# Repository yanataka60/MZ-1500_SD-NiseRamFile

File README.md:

# MZ-1500_SD+偽RAMFILE複合ボード

しっぽいいんちょさんが作られた「偽RAMFILE for MZ-1500」とMZ-1500_SDを合体させたボードです。

MZ-1500_SD: https://github.com/yanataka60/MZ-1500_SD

偽RAMFILE for MZ-1500: https://github.com/shippoiincho/niseramfile

偽RAMFILE for MZ-1500のMZ-1R12 SRAMメモリをMZ-1500_SD起動用に使うことで一枚のボードにまとめています。

機能の詳細についてはそれぞれのウェブページを参照してください。

## 回路図
　KiCadフォルダ内のMZ-1500_SD+NRF.pdfを参照してください。

[回路図](https://github.com/yanataka60/MZ-1500_SD-NiseRamFile/blob/main/Kicad/MZ-1500_SD%2BNRF.pdf)

|番号|品名|数量|備考|
| ------------ | ------------ | ------------ | ------------ |
||J2、J3のいずれか|||
|J2|Micro_SD_Card_Kit|1|秋月電子通商 AE-microSD-LLCNV (注1)|
|J3|MicroSD Card Adapter|1|Arduino等に使われる5V電源に対応したもの(注3)|
|J4,J5|ピンソケット2x15Pin|2|RP2350Bマイコンボード用,秋月電子通商 FHU-2x42SGなど|
|J6|VGA用基板ソケット 3列15ピン|1|マルツ DJ-VGA14.5など(注4)|
|U1|74LS04|1||
|U2|74LS30|1||
|U3|8255|1||
|U4|Arduino_Pro_Mini_5V|1|Atmega328版を使用 168版は不可。(注2)|
||RP2350Bボード(Raspberry Pi Pico 2)|1|Amazon WA00021 RP2350Bマイコンボードなど|
|C1-C3|積層セラミックコンデンサ 0.1uF|3||
|C4|電解コンデンサ 16v100uF|1||
|D1|ダイオード 1N5819|1||
|R1-R3|カーボン抵抗 330Ω|3||
||ピンヘッダ|2Pin分|Arduino_Pro_MiniにはA4、A5用のピンヘッダが付いていないため別途調達が必要です 秋月電子通商 PH-1x40SGなど|
||ピンソケット(任意)|26Pin分|Arduino_Pro_Miniを取り外し可能としたい場合に調達します 秋月電子通商 FHU-1x42SGなど|

　　　注1)秋月電子通商　AE-microSD-LLCNVのJ1ジャンパはショートしてください。

　　　注2)Arduino Pro MiniはA4、A5ピンも使っています。

　　　注3)MicroSD Card Adapterを使う場合

　　　　　J3に取り付けます。

MicroSD Card Adapterについているピンヘッダを除去してハンダ付けするのが一番確実ですが、J3の穴にMicroSD Card Adapterをぴったりと押しつけ、裏から多めにハンダを流し込むことでハンダ付けをする方法もあります。なお、この方法の時にはしっかりハンダ付けが出来たかテスターで導通を確認しておいた方が安心です。

ハンダ付けに自信のない方はJ2の秋月電子通商　AE-microSD-LLCNVをお使いください。AE-microSD-LLCNVならパワーLED、アクセスLEDが付いています。

　　　注4)VGA用基板ソケットには、ピン間隔の異なるものがあるようです。マルツ DJ-VGA14.5ではないものを購入する場合はこちらで寸法を確認してください。

　　　https://www.marutsu.co.jp/contents/shop/marutsu/datasheet/DJ-VGA14.5.pdf

## 偽RAMFILE for MZ-1500の修正
　MZ-1500_SDの起動にはMZ-1R12 SRAMメモリを利用しますが、オリジナルの偽RAMFILE for MZ-1500では電源投入時MZ-1R12 SRAMメモリのチェックでChecksum Errorで止まるようになっていますので電源投入時にMZ-1R12 SRAMメモリから起動できるように修正が必要です。

　niseramfile.cの523行あたりに

//    memcpy(mz1r12,romslots,0x8000);

    memset(mz1r12,0xaa,0x8000);

　となっている個所を

    memcpy(mz1r12,romslots,0x8000);

//    memset(mz1r12,0xaa,0x8000);

　とコメントアウトを修正し、再コンパイルします。

　出来上がったniseramfile.uf2をRP2350Bマイコンボードに書き込みます。

　なお、2026.2.5時点のソースを修正、再コンパイルしたniseramfile.uf2をRP2350Bフォルダに置いてあります。

https://github.com/yanataka60/MZ-1500_SD-NiseRamFile/tree/main/RP2350B

## MZ-1500_SD BOOT PROGRAMをMZ-1R12 SRAMメモリ 0番バックアップスロットへ書き込み
　MZ-1500_SDリポジトリEMMフォルダ内の1Z-009B_SD_Launcher.binをMZ-1R12 SRAMメモリ 0番バックアップスロットへ書き込んでください。

https://github.com/yanataka60/MZ-1500_SD/blob/main/EMM/1Z-009B_SD_Launcher.bin

　書き込み方の詳細は偽RAMFILE for MZ-1500を参照してください。

https://github.com/shippoiincho/niseramfile/tree/main?tab=readme-ov-file#mz-1r12-sram-%E3%83%A1%E3%83%A2%E3%83%AA

　なお、書き込みにpicotool.exeを利用する場合には以下のウェブページ右側の「Releases」からダウンロードできます。

https://github.com/raspberrypi/pico-sdk-tools

## Arduinoプログラム
　MZ-1500_SDを参照してください。

https://github.com/yanataka60/MZ-1500_SD/tree/main?tab=readme-ov-file#arduino%E3%83%97%E3%83%AD%E3%82%B0%E3%83%A9%E3%83%A0

## 運用の注意点
　偽RAMFILE for MZ-1500のEMMは自動的にバックアップされません。

　電源ON時に0番EMMスロットの内容が自動的にEMMにLOADされますが、電源OFF時にEMMの内容は消滅します。

　EMMの内容を書き込み・修正等した場合にはEMMの内容をスロットに書き込む動作を行う必要があります。

https://github.com/shippoiincho/niseramfile/tree/main?tab=readme-ov-file#pio-3034-emm

## EMMからの起動
　「EMM0」に起動可能なMZ-700用HuBASICが存在している場合MZ-1500_SDからコマンド「FDE0」を実行することで「EMM0」のMZ-700用HuBASICから起動可能です。

　なお、EMMの00000番地が「01h」でなければEMMからの起動はせずにコマンド待ちに戻りますが、00000番地以降に異常があってもチェックはしていないので最悪暴走します。

　MZ-1500用HuBASIC、MZ-80K用HuBASICではEMMがサポートされていません。EMMが使えるのはMZ-700用HuBASICのみとなりますが、テープ版しかなくそのままではEMMにHuBASICの起動イメージを作成することが出来ません。

　BouKiCHiさんのHuDiskなどを使いMZ-700用HuBASICの起動ディスクイメージを作成したうえでEMMMENUのEMMLOADでEMMに書き込む必要があります。

## SAMPLEプログラム
　SAMPLEフォルダ内にEMMMENU2を置きました。

　使い方については、フォルダ内のREADME.mdを参照してください。

　SDからEMMへLOAD、EMMの内容をSDへSAVE、EMMスロットからEMMへLOAD、EMMの内容をEMMスロットへSAVEが使えます。

## 謝辞
　素晴らしい拡張モジュールを開発し、複合ボードの公開を快く承諾してくださったしっぽいいんちょさん、ありがとうございました。

## 追記
2026.3.1 MZ-1500_SDリポジトリEMMフォルダ内の1Z-009B_SD_Launcher.binがCHECKSUM計算前のファイルをアップしており、正常起動できませんでしたので更新しました。

2026.3.19 VGA用基板ソケットに注記を追加

2026.6.21 MZ-1500_SD+偽RAMFILE複合ボードに電源が供給されている状態でUSB-Cケーブルを接続してはいけない問題に対してすーぱーたーぼさんからご指摘いただいた対策を施しました。Rev1.0基板でも通常の使用でMZ-1500_SD+偽RAMFILE複合ボードに電源が供給されている状態でUSB-Cケーブルを接続することはありませんので通常使用においてRev1.0基板でも問題ありません。

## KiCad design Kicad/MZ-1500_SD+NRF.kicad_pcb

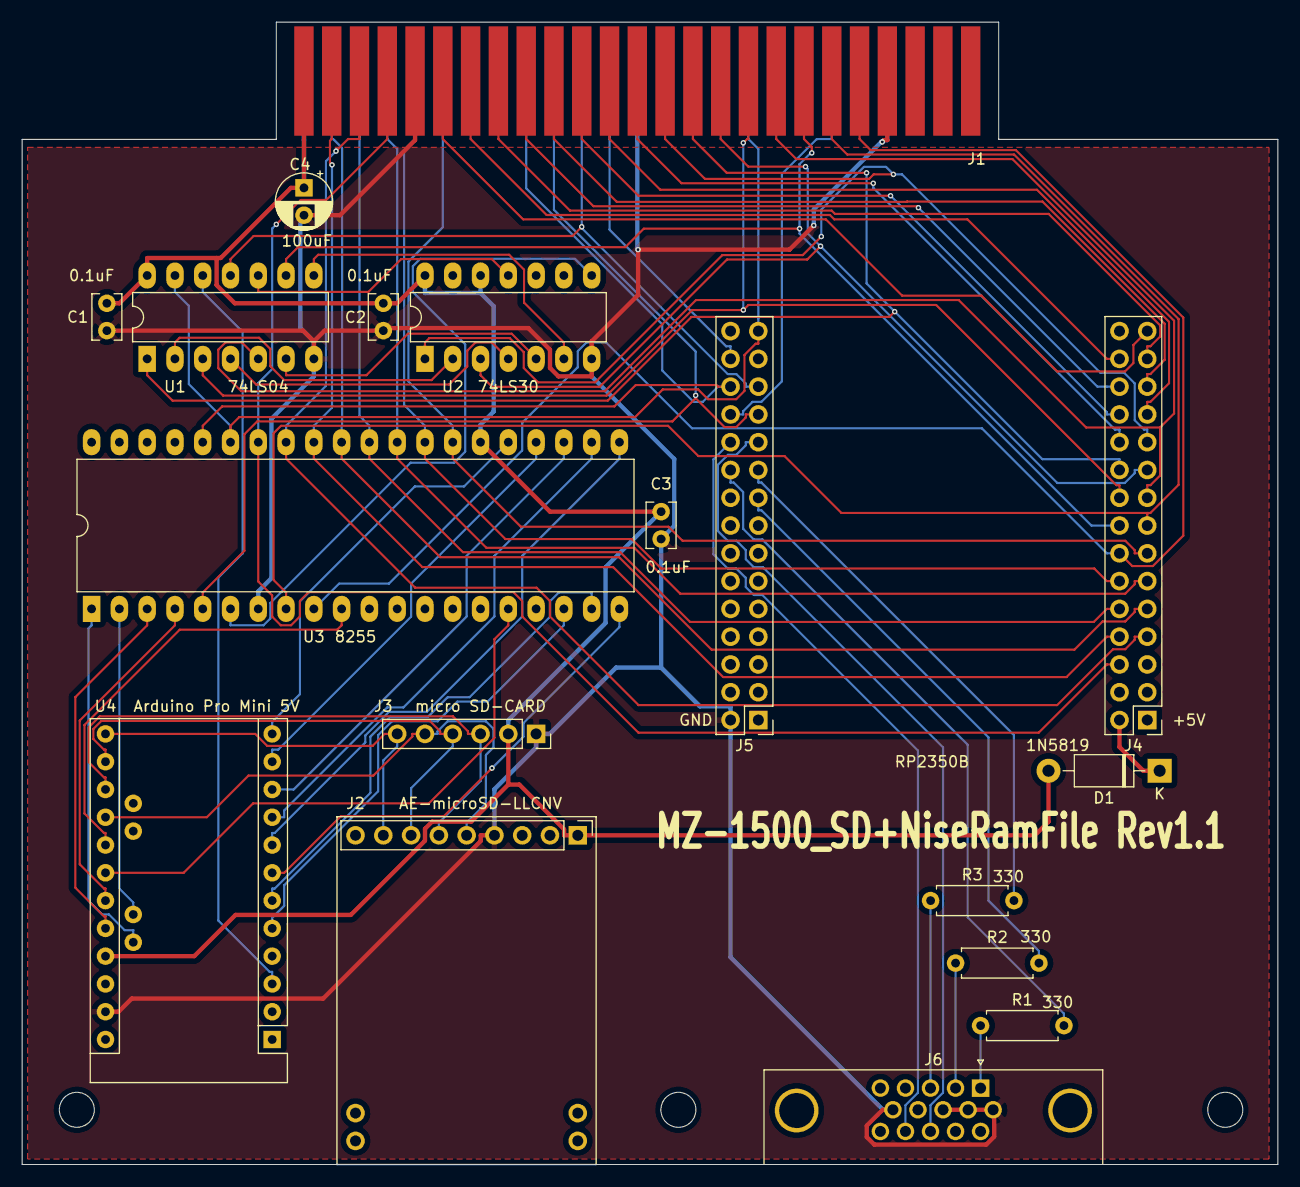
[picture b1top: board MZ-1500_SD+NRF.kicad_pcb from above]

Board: 2 copper layers, 114.8 x 104.4 mm, 21 parts (0 on the bottom side), 66 nets.

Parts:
C1, C2, C3: 0.1uF; C_Rect_L4.0mm_W2.5mm_P2.50mm
C4: 100uF; CP_Radial_D5.0mm_P2.50mm
D1: BAT54; D_DO-41_SOD81_P10.16mm_Horizontal
J1: MZ-1500 BUS; BUS_50Pin
J2: Micro_SD_Card_Kit; AE-microSD-LLCNV
J3: MicroSD Card Adapter; PinSocket_1x06_P2.54mm_Vertical
J4: RP2350B Left; PinHeader_2x15_P2.54mm_Vertical
J5: RP2350B Right; PinHeader_2x15_P2.54mm_Vertical
J6: VGA; DSUB-15-HD_Female_Horizontal_P2.29x1.98mm_EdgePinOffset3.03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
MH1, MH2, MH3: MountingHole_3.2mm_M3
R1, R2, R3: 330; R_Axial_DIN0207_L6.3mm_D2.5mm_P7.62mm_Horizontal
U1: 74LS04; DIP-14_W7.62mm_LongPads
U2: 74LS30; DIP-14_W7.62mm_LongPads
U3: 8255; DIP-40_W15.24mm_LongPads
U4: Arduino_Pro_Mini

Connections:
+5V: C1.1, C2.1, C3.1, C4.1, D1.2, J1.1, J1.2, J2.1, J3.2, U1.14, U2.12, U2.14, U3.26, U4.21
/A0: J1.42, J4.22, U3.9
/A1: J1.40, J4.8, U3.8
/A2: J1.38, J4.23, U1.9
/A3: J1.36, J4.9, U1.5
/A4: J1.34, J4.24, U1.3
/A5: J1.32, J4.10, U2.3
/A6: J1.30, J4.25, U1.1
/A7: J1.28, J4.11, U2.1
/A8: J1.26, J4.26
/A9: J1.24, J4.12
/A10: J1.22, J4.27
/A11: J1.20, J4.13
/A12: J1.18, J4.28
/A13: J1.16, J4.14
/A14: J1.14, J4.29
/A15: J1.12, J4.15
/CS: J2.8, J3.6, U4.13
/D0: J1.8, J4.18, U3.34
/D1: J1.6, J4.4, U3.33
/D2: J1.4, J4.19, U3.32
/D3: J1.3, J4.5, U3.31
/D4: J1.5, J4.20, U3.30
/D5: J1.7, J4.6, U3.29
/D6: J1.9, J4.21, U3.28
/D7: J1.11, J4.7, U3.27
/MISO: J2.6, J3.3, U4.15
/MOSI: J2.7, J3.4, U4.14
/RESET: J1.33, J5.15, U1.13, U3.35
/SCK: J2.5, J3.5, U4.16
/~EXWAIT: J1.39, J5.27
/~IORQ: J1.21, J5.13, U1.11
/~MREQ: J1.23, J5.29
/~RD: J1.19, J5.12, U3.5
/~WR: J1.17, J5.28, U3.36
GND: C1.2, C2.2, C3.2, C4.2, J1.10, J1.25, J1.43, J1.44, J2.4, J3.1, J5.16, J6.6, J6.7, J6.8, J6.10, U1.7, U2.7, U3.7, U4.23
unnamed: D1.1, J4.16
unnamed: J5.9, R2.2
unnamed: J5.10, R3.2
unnamed: J5.11, J6.13
unnamed: J5.25, R1.2
unnamed: J5.26, J6.14
unnamed: J6.1, R1.1
unnamed: J6.2, R2.1
unnamed: J6.3, R3.1
unnamed: U1.2, U2.2
unnamed: U1.4, U2.4
unnamed: U1.6, U2.5
unnamed: U1.8, U2.6
unnamed: U1.10, U2.11
unnamed: U1.12, U4.3
unnamed: U2.8, U3.6
unnamed: U3.1, U4.A5
unnamed: U3.2, U4.A4
unnamed: U3.3, U4.20
unnamed: U3.4, U4.19
unnamed: U3.10, U4.17
unnamed: U3.16, U4.18
unnamed: U3.18, U4.5
unnamed: U3.19, U4.6
unnamed: U3.20, U4.7
unnamed: U3.21, U4.8
unnamed: U3.22, U4.9
unnamed: U3.23, U4.10
unnamed: U3.24, U4.11
unnamed: U3.25, U4.12
